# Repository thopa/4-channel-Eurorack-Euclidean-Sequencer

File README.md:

# 4-channel-Eurorack-Euclidean-Sequencer
4 channel Eurorack Euclidean Sequencer, using Arduino NANO, and modified code from the ARDCORE

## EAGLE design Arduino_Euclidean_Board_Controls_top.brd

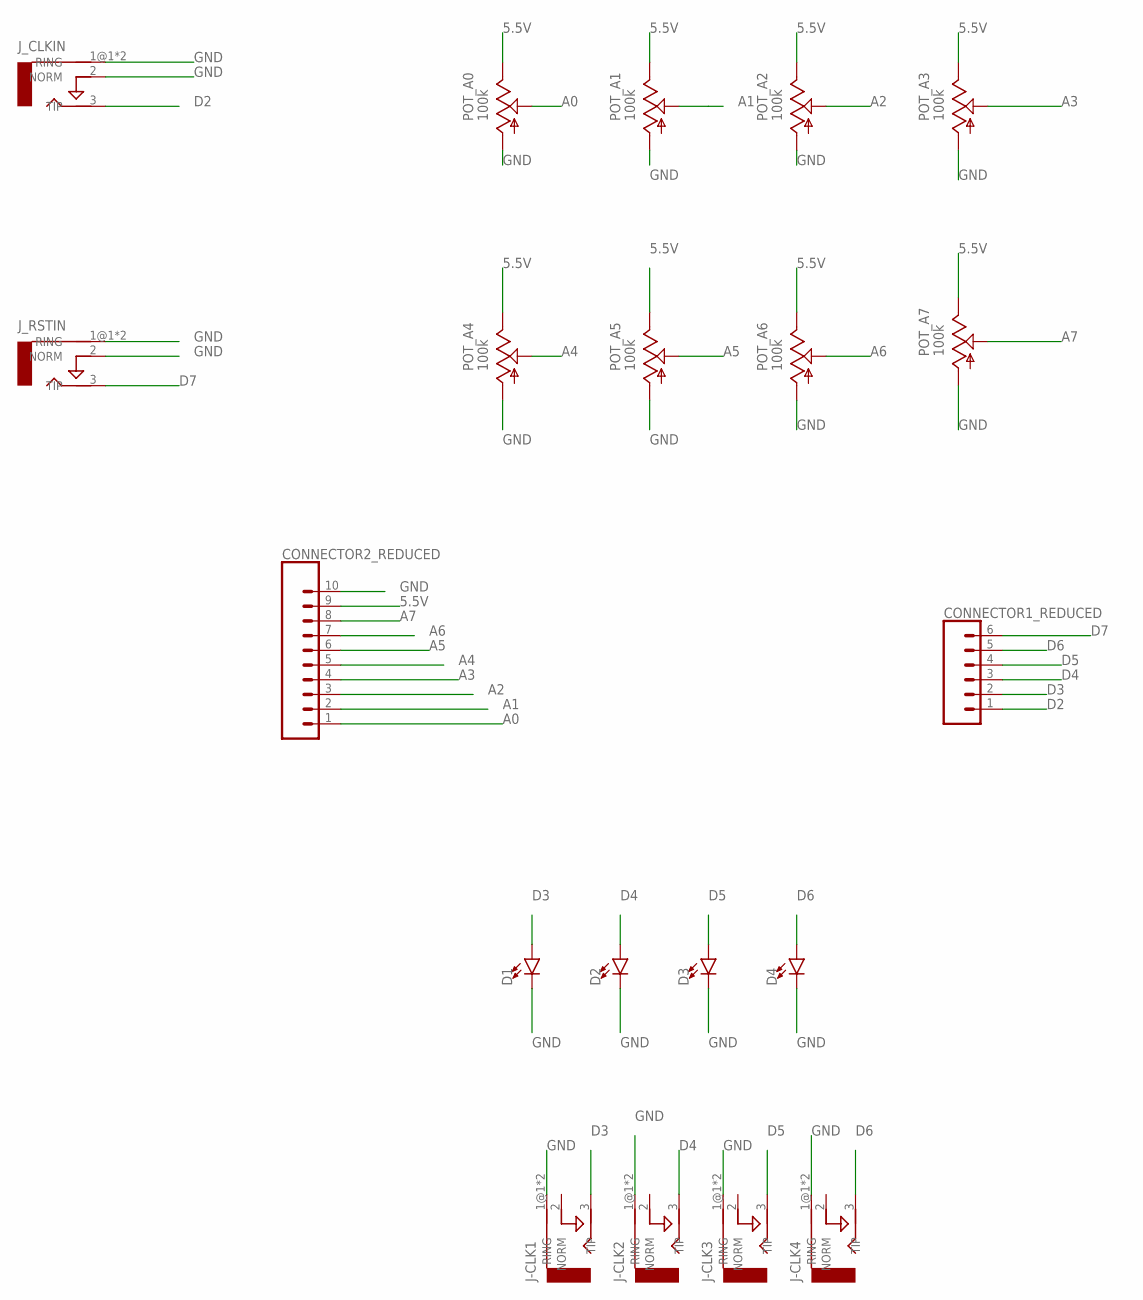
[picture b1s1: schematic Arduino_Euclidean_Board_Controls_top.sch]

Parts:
CONNECTOR1_REDUCED: CONN_06LONGPADS; 1X06_LONGPADS
CONNECTOR2_REDUCED: CONN_10_LONGPADS10_LONGPADS; 1X10_LONGPADS
D1, D2, D3, D4: LED-3MM-NO_SILK; LED_3MM-NS
J-CLK1, J-CLK2, J-CLK3, J-CLK4: AUDIO-JACKERTHENVAR; ERTHENVAR-JACK
J_CLKIN: AUDIO-JACKERTHENVAR; ERTHENVAR-JACK
J_RSTIN: AUDIO-JACKERTHENVAR; ERTHENVAR-JACK
POT_A0, POT_A1, POT_A2, POT_A3, POT_A4, POT_A5, POT_A6, POT_A7: 100k; 9MM_SNAP-IN_POT

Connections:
5.5V: CONNECTOR2_REDUCED.9, POT_A0.3 (E), POT_A1.3 (E), POT_A2.3 (E), POT_A3.3 (E), POT_A4.3 (E), POT_A5.3 (E), POT_A6.3 (E), POT_A7.3 (E)
A0: CONNECTOR2_REDUCED.1, POT_A0.2 (S)
A1: CONNECTOR2_REDUCED.2, POT_A1.2 (S)
A2: CONNECTOR2_REDUCED.3, POT_A2.2 (S)
A3: CONNECTOR2_REDUCED.4, POT_A3.2 (S)
A4: CONNECTOR2_REDUCED.5, POT_A4.2 (S)
A5: CONNECTOR2_REDUCED.6, POT_A5.2 (S)
A6: CONNECTOR2_REDUCED.7, POT_A6.2 (S)
A7: CONNECTOR2_REDUCED.8, POT_A7.2 (S)
D2: CONNECTOR1_REDUCED.1, J_CLKIN.3 (TIP)
D3: CONNECTOR1_REDUCED.2, D1.A, J-CLK1.3 (TIP)
D4: CONNECTOR1_REDUCED.3, D2.A, J-CLK2.3 (TIP)
D5: CONNECTOR1_REDUCED.4, D3.A, J-CLK3.3 (TIP)
D6: CONNECTOR1_REDUCED.5, D4.A, J-CLK4.3 (TIP)
D7: CONNECTOR1_REDUCED.6, J_RSTIN.3 (TIP)
GND: CONNECTOR2_REDUCED.10, D1.K (C), D2.K (C), D3.K (C), D4.K (C), J-CLK1.1@1 (RING), J-CLK1.1@2 (RING), J-CLK2.1@1 (RING), J-CLK2.1@2 (RING), J-CLK3.1@1 (RING), J-CLK3.1@2 (RING), J-CLK4.1@1 (RING), J-CLK4.1@2 (RING), J_CLKIN.1@1 (RING), J_CLKIN.1@2 (RING), J_CLKIN.2 (NORM), J_RSTIN.1@1 (RING), J_RSTIN.1@2 (RING), J_RSTIN.2 (NORM), POT_A0.1 (A), POT_A1.1 (A), POT_A2.1 (A), POT_A3.1 (A), POT_A4.1 (A), POT_A5.1 (A), POT_A6.1 (A), POT_A7.1 (A)

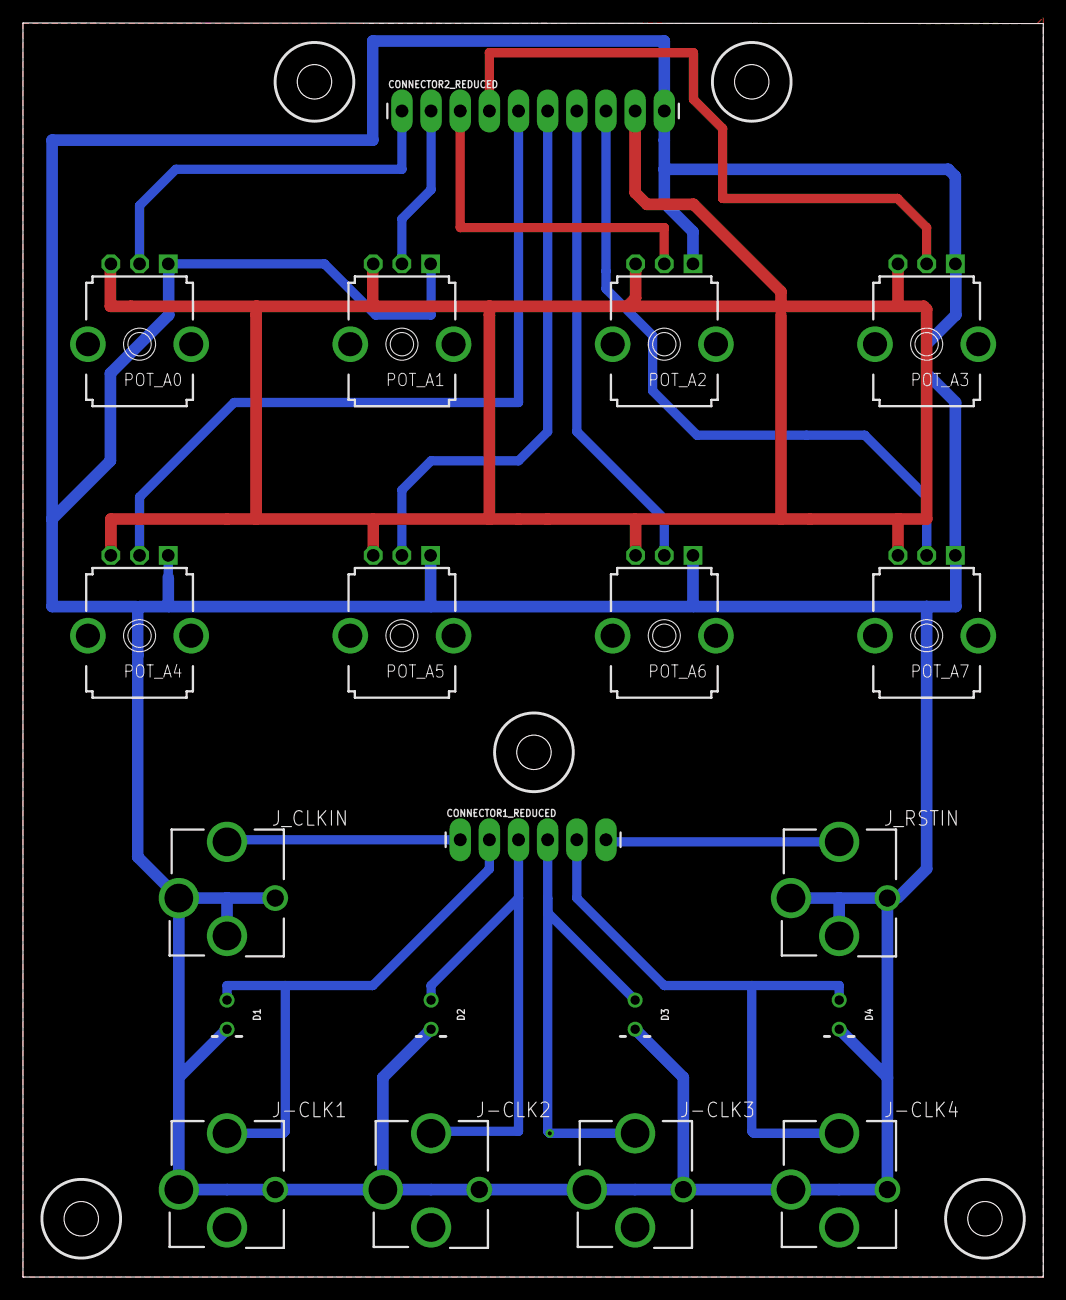
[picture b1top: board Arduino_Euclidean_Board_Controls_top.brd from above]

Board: 2 copper layers, 88.9 x 109.3 mm, 25 parts (0 on the bottom side), 16 nets.

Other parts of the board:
H1, H2, H3, H4, H5: DRIL-3

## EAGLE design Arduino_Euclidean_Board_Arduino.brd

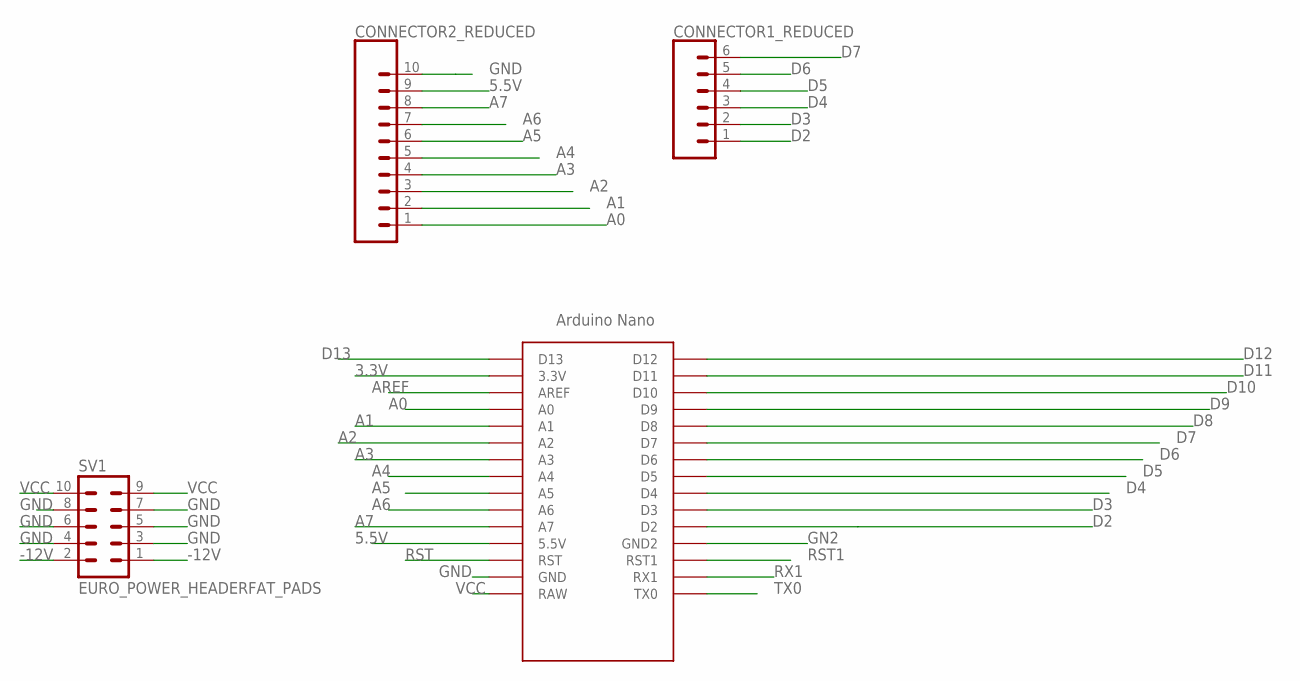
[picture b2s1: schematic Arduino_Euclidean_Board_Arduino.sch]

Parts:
CONNECTOR1_REDUCED: CONN_06LONGPADS; 1X06_LONGPADS
CONNECTOR2_REDUCED: CONN_10_LONGPADS10_LONGPADS; 1X10_LONGPADS
SV1: EURO_POWER_HEADERFAT_PADS; EURO_PWR_HEADER_FAT
U$1: NANO

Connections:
3.3V: U$1.3.3V
5.5V: CONNECTOR2_REDUCED.9, U$1.5V (5.5V)
-12V: SV1.1, SV1.2
A0: CONNECTOR2_REDUCED.1, U$1.A0
A1: CONNECTOR2_REDUCED.2, U$1.A1
A2: CONNECTOR2_REDUCED.3, U$1.A2
A3: CONNECTOR2_REDUCED.4, U$1.A3
A4: CONNECTOR2_REDUCED.5, U$1.A4
A5: CONNECTOR2_REDUCED.6, U$1.A5
A6: CONNECTOR2_REDUCED.7, U$1.A6
A7: CONNECTOR2_REDUCED.8, U$1.A7
AREF: U$1.AREF
D2: CONNECTOR1_REDUCED.1, U$1.D2
D3: CONNECTOR1_REDUCED.2, U$1.D3
D4: CONNECTOR1_REDUCED.3, U$1.D4
D5: CONNECTOR1_REDUCED.4, U$1.D5
D6: CONNECTOR1_REDUCED.5, U$1.D6
D7: CONNECTOR1_REDUCED.6, U$1.D7
D8: U$1.D8
D9: U$1.D9
D10: U$1.D10
D11: U$1.D11
D12: U$1.D12
D13: U$1.D13
GN2: U$1.GND1 (GND2)
GND: CONNECTOR2_REDUCED.10, SV1.3, SV1.4, SV1.5, SV1.6, SV1.7, SV1.8, U$1.GND
RST: U$1.RST
RST1: U$1.RST1
RX1: U$1.RX1
TX0: U$1.TX0
VCC: SV1.9, SV1.10, U$1.RAW

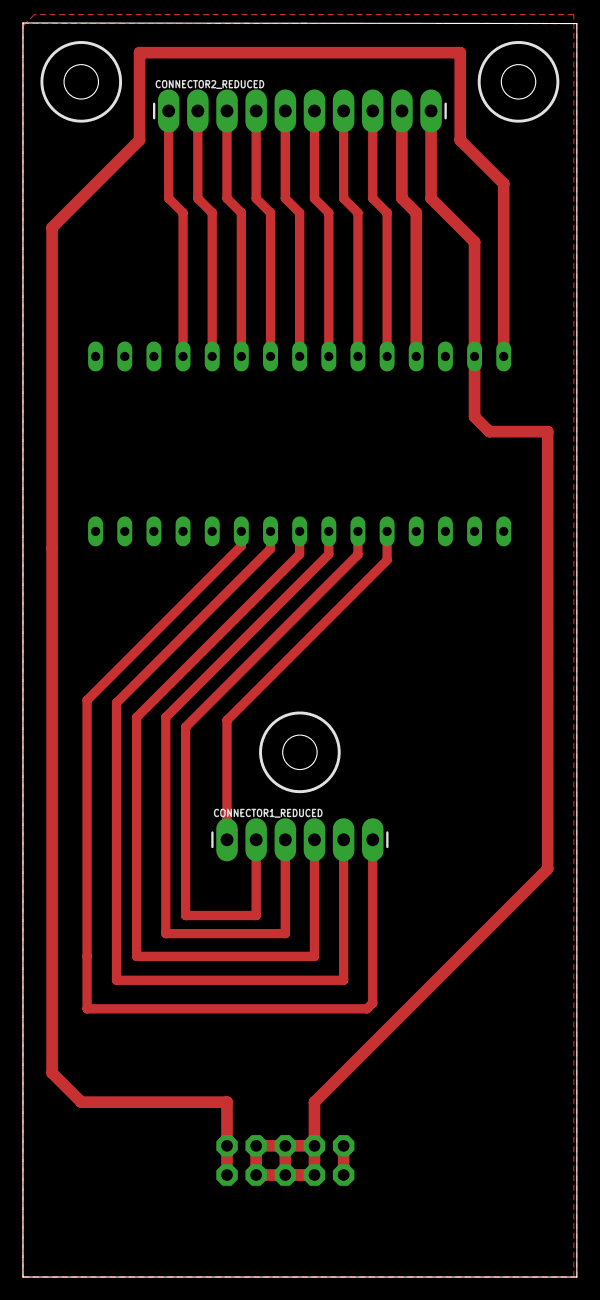
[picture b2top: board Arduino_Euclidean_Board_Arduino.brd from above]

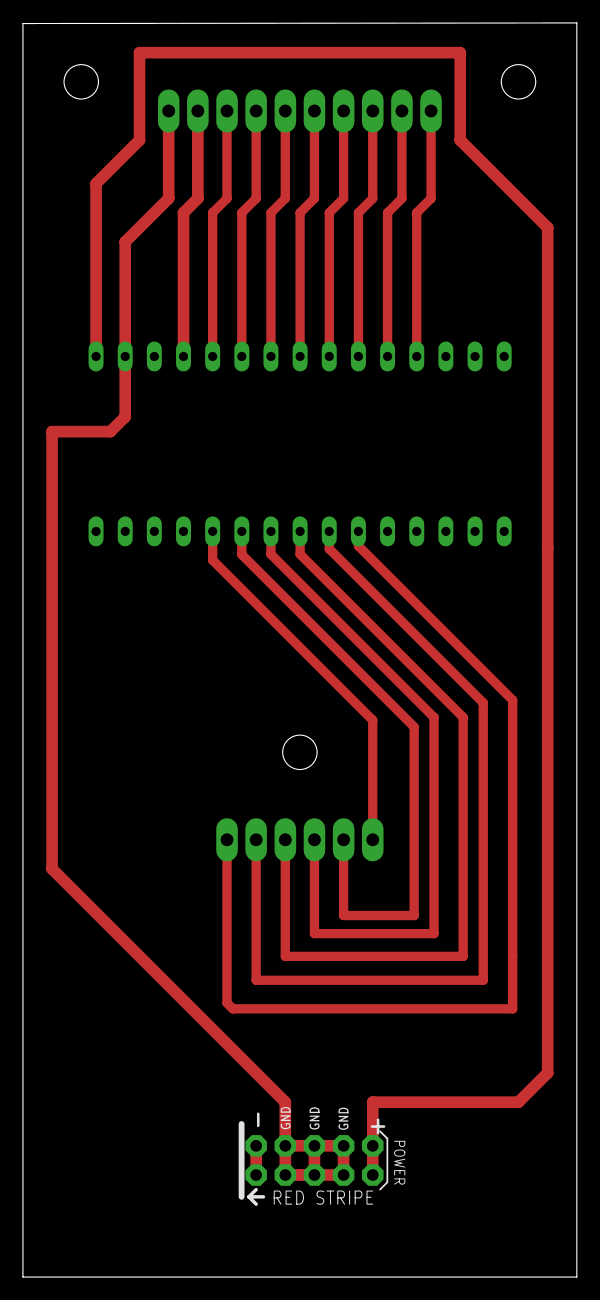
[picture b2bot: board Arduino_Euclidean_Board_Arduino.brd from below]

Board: 2 copper layers, 48.3 x 109.3 mm, 7 parts (2 on the bottom side), 18 nets.

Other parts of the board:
H1, H2, H4: DRIL-3

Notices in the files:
parts and their libraries:
SparkFun-Connectors: Licensing: Creative Commons ShareAlike 4.0 International - https://creativecommons.org/licenses/by-sa/4.0
